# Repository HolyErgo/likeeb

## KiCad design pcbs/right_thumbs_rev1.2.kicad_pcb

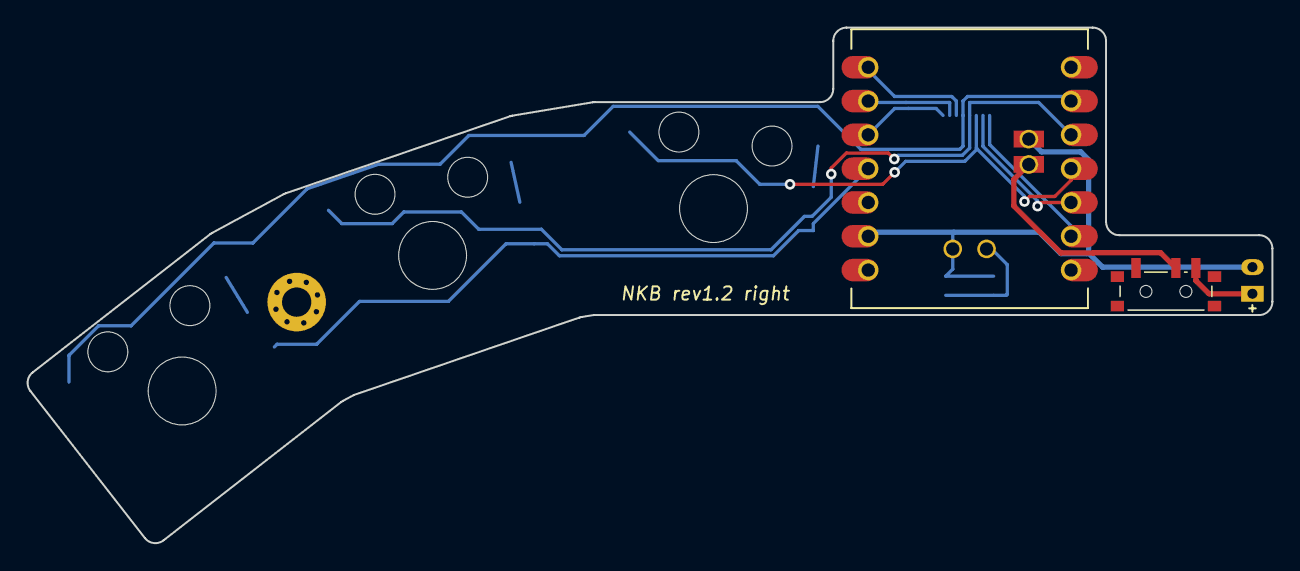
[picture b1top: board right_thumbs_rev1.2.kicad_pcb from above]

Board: 2 copper layers, 93.5 x 38.7 mm, 8 parts (1 on the bottom side), 5 nets.

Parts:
BAT1: BatteryPad
S1, S2, S3: GateronLowProfileSwitch
SW1: power_switch
SW2: sw_reset_side
_2: HKWClamshellSocket
_3: MountingHole_2.2mm_M2_Pad_Via

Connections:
CT6: S3.1, _2.4
CT7: S2.1, _2.5
CT8: S1.1, _2.6
RBAT_P: BAT1.1, SW1.3
RGND: BAT1.2, SW2.1

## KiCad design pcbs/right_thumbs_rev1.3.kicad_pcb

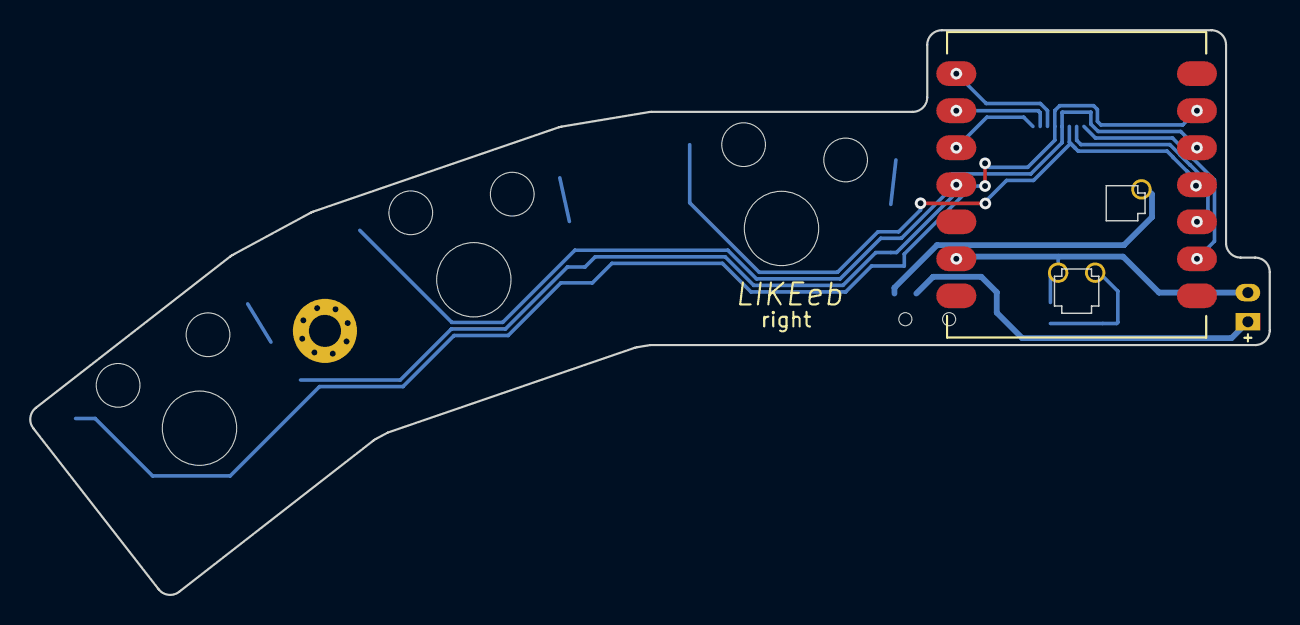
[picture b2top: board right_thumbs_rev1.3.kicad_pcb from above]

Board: 2 copper layers, 85.0 x 38.7 mm, 8 parts (1 on the bottom side), 9 nets.

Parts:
BAT1: BatteryPad
S1, S2, S3: GateronLowProfileSwitch
SW2: sw_reset_side
_1: Seeeduino XIAO nRF52840
_2: HKW FPC Socket
_3: MountingHole_2.2mm_M2_Pad_Via

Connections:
CT6: S3.1, _1.6, _2.4
CT7: S2.1, _1.5, _2.5
CT8: S1.1, _1.4, _2.6
CT9: _1.3, _2.7
CT10: _1.2, _2.8
RGND: BAT1.2, SW2.1, _1.13
RRT1: _1.8, _2.3
RRT2: _1.9, _2.2
RRT3: _1.10, _2.1
